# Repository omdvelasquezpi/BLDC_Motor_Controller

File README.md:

# Sistema de monitorización de los parámetros de un vehículo eléctrico

Este repositorio documenta el desarrollo de un sistema de monitorización de parámetros de un motor DC sin escobillas, tales como, la temperatura de la batería, la corriente de entrada, el estado de carga de la batería, entre otros, utilizando un sistema embebido con una ESP32. El desarrollo del proyecto se realiza para la asignatura de Sistemas Embebidos en la Universidad Nacional de Colombia.

# Integrantes del grupo

- Sharon Damara Peñaloza Restrepo.
- Jhon Edison Ríos Fonseca.
- Renzo Agusto Lopez Castillo.
- Omar David Velásquez Pinto.

# Ideación del proyecto

En principio, el proyecto hace parte del desarrollo de un vehículo eléctrico altamente eficiente, desarrollado por la Universidad Nacional de Colombia para la competencia internacional de la [Shell Eco Marathon](https://www.makethefuture.shell/en-gb/shell-eco-marathon). Esta competencia se desarrolla anualmente y en ella participan universidades de todo el mundo para promover la movilidad ultra-eficiente. 

Para el diseño y construcción del vehículo de la UNAL, se reúnen estudiantes de distintas áreas del conocimiento para aportar conceptos de STEM (Science, Technology, Engineering and Math) formando el grupo estudiantil STEOS (Sistemas de Transporte Eléctricos Óptimos y Sostenibles) (Enlaces de interés: [Facebook](https://www.facebook.com/Steos-113420670376989), [Instagram](https://www.instagram.com/steos.unal/?hl=es), [YouTube](https://www.youtube.com/channel/UCcqXOqdHFdif6k-UERizOug)), que busca promover la movilidad eléctrica y su implementación en Colombia. Este grupo está formado por las áreas de Diseño (Gráfico e Industrial), Ingeniería Mecánica e Ingeniería Electrónica.

En el marco de este proyecto, desde el área de Ingeniería Electrónica se ha desarrollado el sistema electrónico de [Sharky](https://www.youtube.com/watch?v=2vRT9TGoiSc&t=315s) (vehículo eléctrico de STEOS), que abarca tres principales etapas: Almacenamiento, Control y Propulsión. Teniendo en cuenta el alcance de la asignatura y las necesidades de diseño expuestas a continuación, el presente repositorio documenta el diseño de la etapa de Control de parámetros.

# Requerimientos del cliente y alcance

- [Reglamento de la competencia](https://base.makethefuture.shell/en_gb/service/api/home/shell-eco-marathon/global-rules/_jcr_content/root/content/document_listing/items/download_595134961.stream/1630485146156/38a7abe7331aaa24603d0e8b158565cc726ab78d/shell-eco-marathon-2022-official-rules-chapter-i.pdf).
- Diseño mecánico del vehículo y espacio disponible para montar el sistema.
- Características del motor ([mecánicas](https://ebikes.ca/documents/MG310.pdf) y [eléctricas](https://motowoks.com/products/bafang-rm-g310-250-dc-rear-drive-motor-250w)).
- Características de la batería ().
- Capacidad del piloto para variar la velocidad.

# Diagrama de bloques

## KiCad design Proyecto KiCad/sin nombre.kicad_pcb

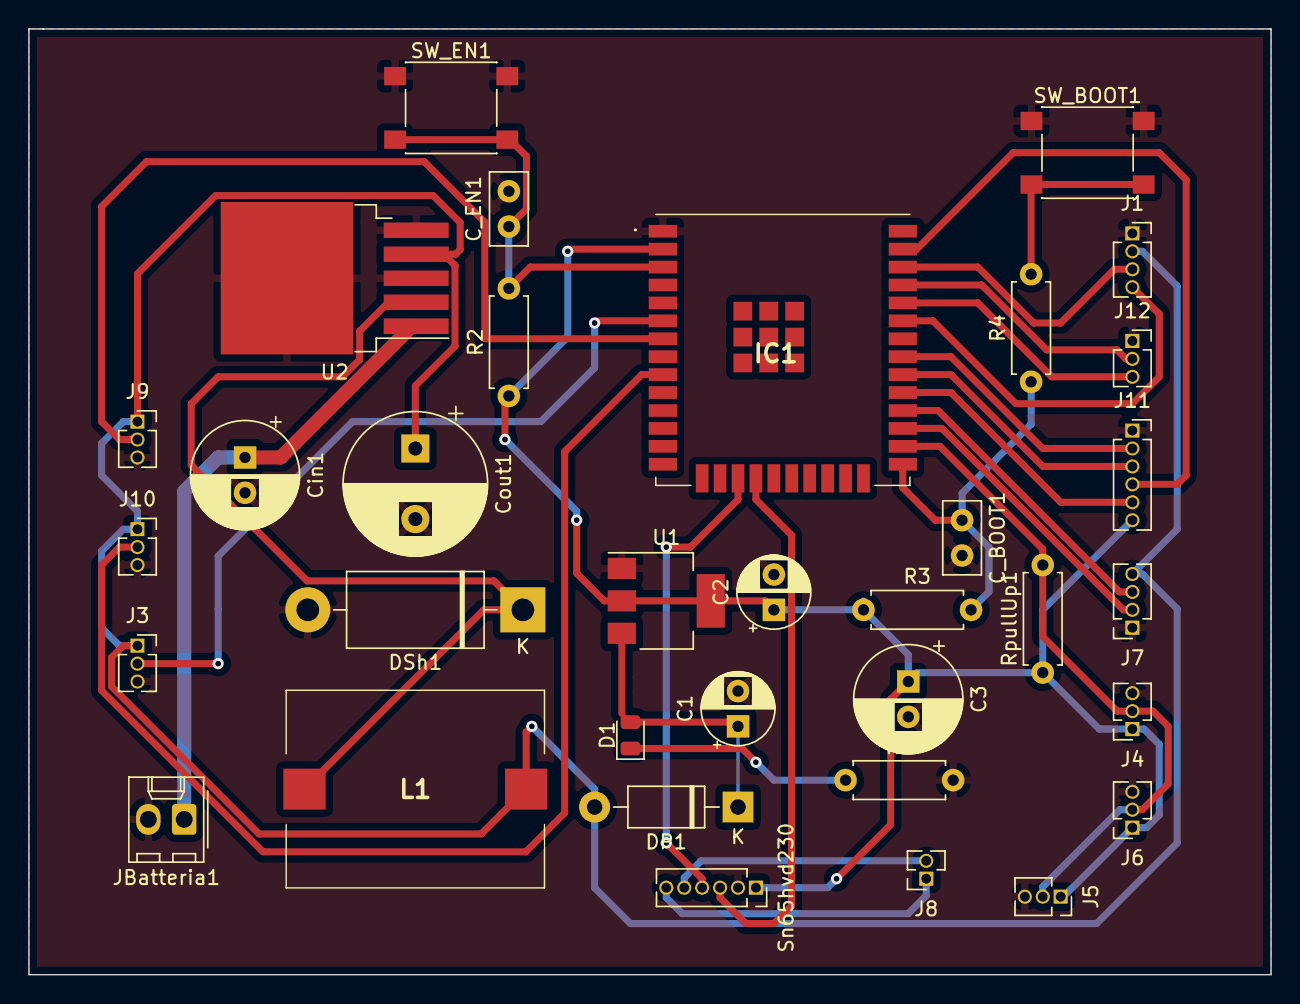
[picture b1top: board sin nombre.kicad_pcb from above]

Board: 2 copper layers, 88.0 x 67.0 mm, 34 parts (0 on the bottom side), 28 nets.

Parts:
C1, C2: 10u; CP_Radial_D5.0mm_P2.50mm
C3: 100u; CP_Radial_D7.5mm_P2.50mm
C_BOOT1: 100nF; C_Disc_D5.0mm_W2.5mm_P2.50mm
C_EN1: 100nF; C_Disc_D5.0mm_W2.5mm_P2.50mm
Cin1: 100uF; CP_Radial_D7.5mm_P2.50mm
Cout1: 1000uF; CP_Radial_D10.0mm_P5.00mm
D1: LED; LED_0805_2012Metric
DP1: 1N5819; D_DO-41_SOD81_P10.16mm_Horizontal
DSh1: 1N5822; D_DO-201AD_P15.24mm_Horizontal
IC1: ESP32-WROOM-32D_M113DH2800PH3Q0_; ESP32WROOM32DM113DH2800PH3Q0
J1: I2C; PinSocket_1x04_P1.27mm_Vertical
J3: Connector Sensor Corriente Carga; PinSocket_1x03_P1.27mm_Vertical
J4: Connector Sensor Temp 1; PinSocket_1x03_P1.27mm_Vertical
J5: Connector Sensor Temp 2; PinSocket_1x03_P1.27mm_Vertical
J6: Connector Sensor Temp 3; PinSocket_1x03_P1.27mm_Vertical
J7: LCD; PinSocket_1x04_P1.27mm_Vertical
J8: Conn_01x02; PinSocket_1x02_P1.27mm_Vertical
J9: Connector Sensor Corriente Descarga; PinSocket_1x03_P1.27mm_Vertical
J10: Connector Sensor Voltaje; PinSocket_1x03_P1.27mm_Vertical
J11: Conector MicroSD; PinSocket_1x06_P1.27mm_Vertical
J12: USB_TTL; PinSocket_1x03_P1.27mm_Vertical
JBatteria1: Conn_01x02_Male; Molex_KK-254_AE-6410-02A_1x02_P2.54mm_Vertical
L1: SDR1806-101KL; SDR1806101KL
R1: 1k; R_Axial_DIN0207_L6.3mm_D2.5mm_P7.62mm_Horizontal
R2, R3: 10k; R_Axial_DIN0207_L6.3mm_D2.5mm_P7.62mm_Horizontal
R4: 470; R_Axial_DIN0207_L6.3mm_D2.5mm_P7.62mm_Horizontal
RpullUp1: 4.7k; R_Axial_DIN0207_L6.3mm_D2.5mm_P7.62mm_Horizontal
SW_BOOT1: SW_Push; SW_Push_1P1T_NO_6x6mm_H9.5mm
SW_EN1: SW_Push; SW_Push_1P1T_NO_6x6mm_H9.5mm
Sn65hvd230: TransceptorCanBus; PinSocket_1x06_P1.27mm_Vertical
U1: AMS1117; SOT-223-3_TabPin2
U2: LM2576S-5; TO-263-5_TabPin3

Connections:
5VReg: Cout1.1, DP1.2, J1.2, J3.1, J7.4, J9.1, J10.1, L1.2, U2.4
36V: Cin1.1, JBatteria1.1, U2.1
BOOT: C_BOOT1.1, IC1.25, R3.2, R4.1
CAN_CRX: IC1.17, Sn65hvd230.4
CAN_CTX: IC1.18, Sn65hvd230.3
CS_microSD: IC1.29, J11.5
EN: C_EN1.1, IC1.3, R2.2, SW_EN1.2
GND: C1.2, C2.2, C3.2, C_BOOT1.2, C_EN1.2, Cin1.2, Cout1.2, DSh1.2, IC1.1, J1.1, J3.3, J4.3, J5.3, J6.3, J7.1, J9.3, J10.3, J11.1, J12.1, JBatteria1.2, R1.2, SW_BOOT1.1, SW_EN1.1, Sn65hvd230.2, U1.1, U2.3, U2.5
MISO_micSD: IC1.31, J11.2
MOSI_micSD: IC1.37, J11.4
unnamed: D1.1, R1.1
unnamed: DSh1.1, L1.1, U2.2
unnamed: J8.1, Sn65hvd230.6
unnamed: J8.2, Sn65hvd230.5
unnamed: R4.2, SW_BOOT1.2
OutSensorCC: IC1.6, J3.2
OutSensorCD: IC1.7, J9.2
OutSensorTemp: IC1.26, J4.2, J5.2, J6.2, RpullUp1.2
OutSensorV: IC1.9, J10.2
RX-LCD: IC1.27, J7.2
RXD0: IC1.34, J12.3
SCK_micSD: IC1.30, J11.3
SCL: IC1.36, J1.3
SDA: IC1.33, J1.4
TX-LCD: IC1.28, J7.3
TXD0: IC1.35, J12.2
V3V3: C2.1, C3.1, IC1.2, J4.1, J5.1, J6.1, J11.6, R2.1, R3.1, RpullUp1.1, Sn65hvd230.1, U1.2
V5V: C1.1, D1.2, DP1.1, U1.3

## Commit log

2022-07-06 Create Datasheets
2022-07-07 Rios
